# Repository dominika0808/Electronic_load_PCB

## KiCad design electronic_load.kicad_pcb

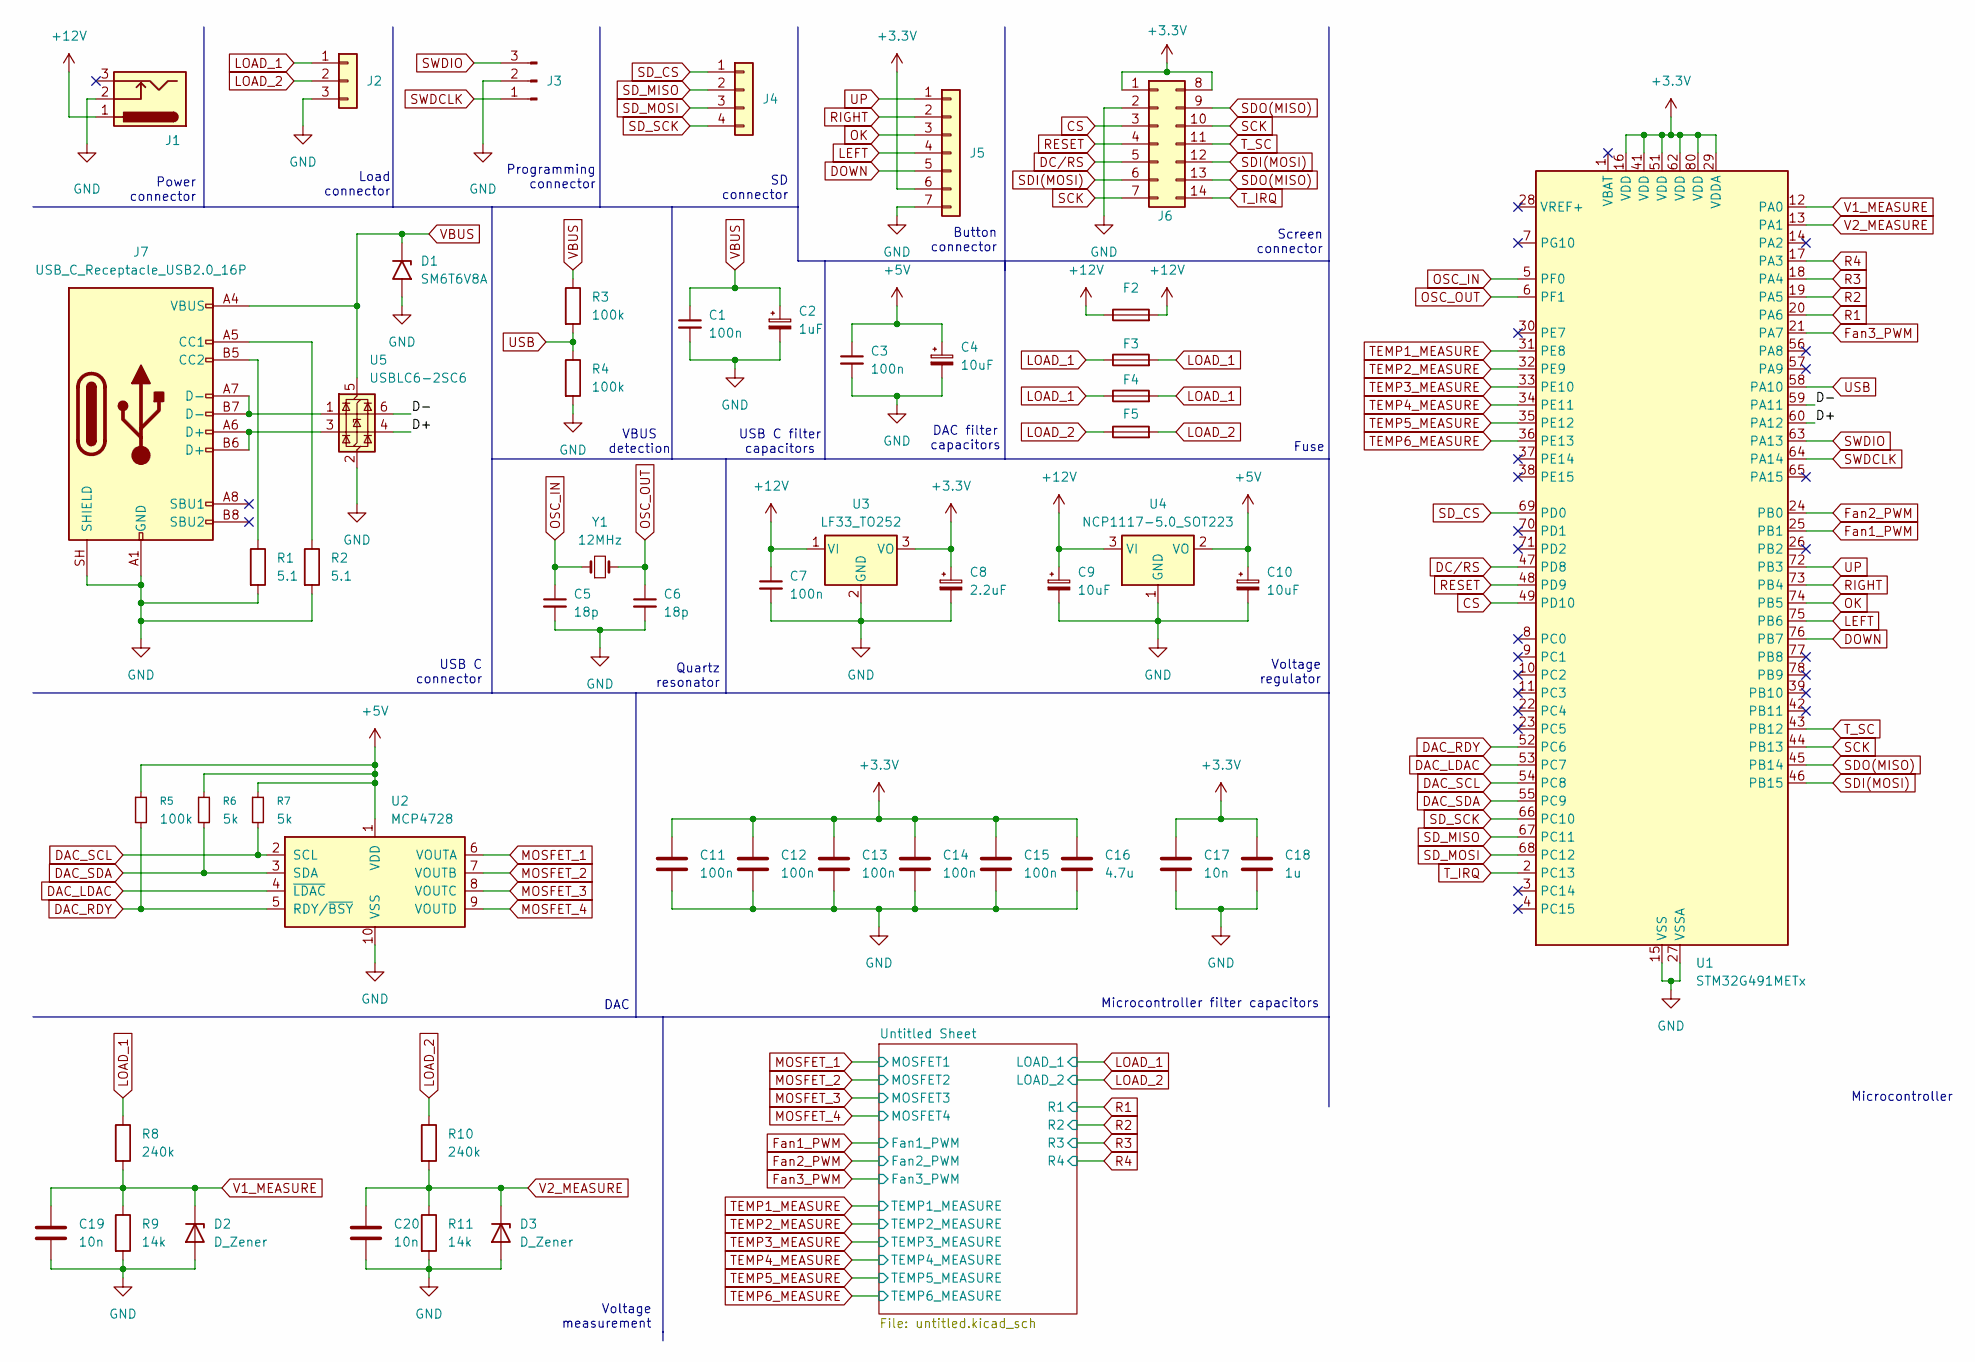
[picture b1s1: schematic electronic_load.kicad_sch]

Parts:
C1, C3, C7, C11, C12, C13, C14, C15: 100n; C_0805_2012Metric_Pad1.18x1.45mm_HandSolder
C2: 1uF; CP_EIA-3216-18_Kemet-A_HandSolder
C4: 10uF; CP_EIA-3216-18_Kemet-A_HandSolder
C5, C6: 18p; C_0805_2012Metric_Pad1.18x1.45mm_HandSolder
C8: 2.2uF; C_Elec_4x5.4
C9, C10: 10uF; C_Elec_4x5.8
C16: 4.7u; C_0805_2012Metric_Pad1.18x1.45mm_HandSolder
C17, C19, C20: 10n; C_0805_2012Metric_Pad1.18x1.45mm_HandSolder
C18: 1u; C_0805_2012Metric_Pad1.18x1.45mm_HandSolder
D1: SM6T6V8A; D_SMB
D2, D3: D_Zener; D_SOD-123F
F2, F3, F4, F5: Fuse; Fuse_1206_3216Metric_Pad1.42x1.75mm_HandSolder
J1: Barrel_Jack_Switch_Pin3Ring; BarrelJack_Wuerth_694106106102_2.0x5.5mm
J2: Conn_01x03; TerminalBlock_MaiXu_MX126-5.0-03P_1x03_P5.00mm
J3: Conn_01x03_Pin; PinHeader_1x03_P2.54mm_Vertical
J4: Conn_01x04; JST_EH_B4B-EH-A_1x04_P2.50mm_Vertical
J5: Conn_01x07; JST_EH_B7B-EH-A_1x07_P2.50mm_Vertical
J6: Conn_02x07_Top_Bottom; JST_PHD_B14B-PHDSS_2x07_P2.00mm_Vertical
J7: USB_C_Receptacle_USB2.0_16P; USB_C_Receptacle_GCT_USB4105-xx-A_16P_TopMnt_Horizontal
R1, R2: 5.1; R_0805_2012Metric_Pad1.20x1.40mm_HandSolder
R3, R4, R5: 100k; R_0805_2012Metric_Pad1.20x1.40mm_HandSolder
R6, R7: 5k; R_0805_2012Metric_Pad1.20x1.40mm_HandSolder
R8, R10: 240k; R_0805_2012Metric_Pad1.20x1.40mm_HandSolder
R9, R11: 14k; R_0805_2012Metric_Pad1.20x1.40mm_HandSolder
U1: STM32G491METx; LQFP-80_12x12mm_P0.5mm
U2: MCP4728; MSOP-10_3x3mm_P0.5mm
U3: LF33_TO252; TO-252-2
U4: NCP1117-5.0_SOT223; SOT-223-3_TabPin2
U5: USBLC6-2SC6; SOT-23-6
Y1: 12MHz; Crystal_HC49-4H_Vertical

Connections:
+3.3V: C8.1, C11.1, C12.1, C13.1, C14.1, C15.1, C16.1, C17.1, C18.1, J5.6, J6.1, J6.8, U1.16 (VDD), U1.29 (VDDA), U1.41 (VDD), U1.51 (VDD), U1.62 (VDD), U1.80 (VDD), U3.3 (VO); also elsewhere on the board
+5V: C3.1, C4.1, C10.1, R5.1, R6.1, R7.1, U2.1 (VDD), U4.2 (VO)
+12V: C7.1, C9.1, F2.1, F2.2, J1.1, U3.1 (VI), U4.3 (VI); also elsewhere on the board
/D+: U1.60 (PA12), U5.4 (I/O2)
/D-: U1.59 (PA11), U5.6 (I/O1)
CS: J6.3, U1.49 (PD10)
DAC_LDAC: U1.53 (PC7), U2.4 (~LDAC)
DAC_RDY: R5.2, U1.52 (PC6), U2.5 (RDY/~BSY)
DAC_SCL: R7.2, U1.54 (PC8), U2.2 (SCL)
DAC_SDA: R6.2, U1.55 (PC9), U2.3 (SDA)
DC/RS: J6.5, U1.47 (PD8)
DOWN: J5.5, U1.76 (PB7)
Fan1_PWM: U1.25 (PB1); also elsewhere on the board
Fan2_PWM: U1.24 (PB0); also elsewhere on the board
Fan3_PWM: U1.21 (PA7); also elsewhere on the board
GND: C1.2, C2.2, C3.2, C4.2, C5.2, C6.2, C7.2, C8.2, C9.2, C10.2, C11.2, C12.2, C13.2, C14.2, C15.2, C16.2, C17.2, C18.2, C19.2, C20.2, D1.2 (A2), D2.2 (A), D3.2 (A), J1.2, J2.3, J3.2, J5.7, J6.2, J7.A1 (GND), J7.A12 (GND), J7.B1 (GND), J7.B12 (GND), J7.SH (SHIELD), R1.2, R2.2, R4.2, R9.2, R11.2, U1.15 (VSS), U1.27 (VSSA), U1.40 (VSS), U1.50 (VSS), U1.61 (VSS), U1.79 (VSS), U2.10 (VSS), U3.2 (GND), U4.1 (GND), U5.2 (GND); also elsewhere on the board
LEFT: J5.4, U1.75 (PB6)
LOAD_1: F3.1, F3.2, F4.1, F4.2, J2.1, R8.1; also elsewhere on the board
LOAD_2: F5.1, F5.2, J2.2, R10.1; also elsewhere on the board
MOSFET_1: U2.6 (VOUTA); also elsewhere on the board
MOSFET_2: U2.7 (VOUTB); also elsewhere on the board
MOSFET_3: U2.8 (VOUTC); also elsewhere on the board
MOSFET_4: U2.9 (VOUTD); also elsewhere on the board
unnamed: J7.A5 (CC1), R2.1
unnamed: J7.B5 (CC2), R1.1
unnamed: J7.A6 (D+), J7.B6 (D+), U5.3 (I/O2)
unnamed: J7.A7 (D-), J7.B7 (D-), U5.1 (I/O1)
OK: J5.3, U1.74 (PB5)
OSC_IN: C5.1, U1.5 (PF0), Y1.1
OSC_OUT: C6.1, U1.6 (PF1), Y1.2
R1: U1.20 (PA6); also elsewhere on the board
R2: U1.19 (PA5); also elsewhere on the board
R3: U1.18 (PA4); also elsewhere on the board
R4: U1.17 (PA3); also elsewhere on the board
RESET: J6.4, U1.48 (PD9)
RIGHT: J5.2, U1.73 (PB4)
SCK: J6.7, J6.10, U1.44 (PB13)
SDI(MOSI): J6.6, J6.12, U1.46 (PB15)
SDO(MISO): J6.9, J6.13, U1.45 (PB14)
SD_CS: J4.1, U1.69 (PD0)
SD_MISO: J4.2, U1.67 (PC11)
SD_MOSI: J4.3, U1.68 (PC12)
SD_SCK: J4.4, U1.66 (PC10)
SWDCLK: J3.1, U1.64 (PA14)
SWDIO: J3.3, U1.63 (PA13)
TEMP1_MEASURE: U1.31 (PE8); also elsewhere on the board
TEMP2_MEASURE: U1.32 (PE9); also elsewhere on the board
TEMP3_MEASURE: U1.33 (PE10); also elsewhere on the board
TEMP4_MEASURE: U1.34 (PE11); also elsewhere on the board
TEMP5_MEASURE: U1.35 (PE12); also elsewhere on the board
TEMP6_MEASURE: U1.36 (PE13); also elsewhere on the board
T_IRQ: J6.14, U1.2 (PC13)
T_SC: J6.11, U1.43 (PB12)
UP: J5.1, U1.72 (PB3)
USB: R3.2, R4.1, U1.58 (PA10)
V1_MEASURE: C19.1, D2.1 (K), R8.2, R9.1, U1.12 (PA0)
V2_MEASURE: C20.1, D3.1 (K), R10.2, R11.1, U1.13 (PA1)
VBUS: C1.1, C2.1, D1.1 (A1), J7.A4 (VBUS), J7.A9 (VBUS), J7.B4 (VBUS), J7.B9 (VBUS), R3.1, U5.5 (VBUS)

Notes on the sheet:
Microcontroller
Screen connector
Voltage regulator
DAC
USB C connector
USB C filter capacitors
Load connector
Voltage measurement
DAC filter capacitors
Microcontroller filter capacitors
Programming connector
Quartz resonator
Fuse
SD connector
Power connector
VBUS detection
Button connector

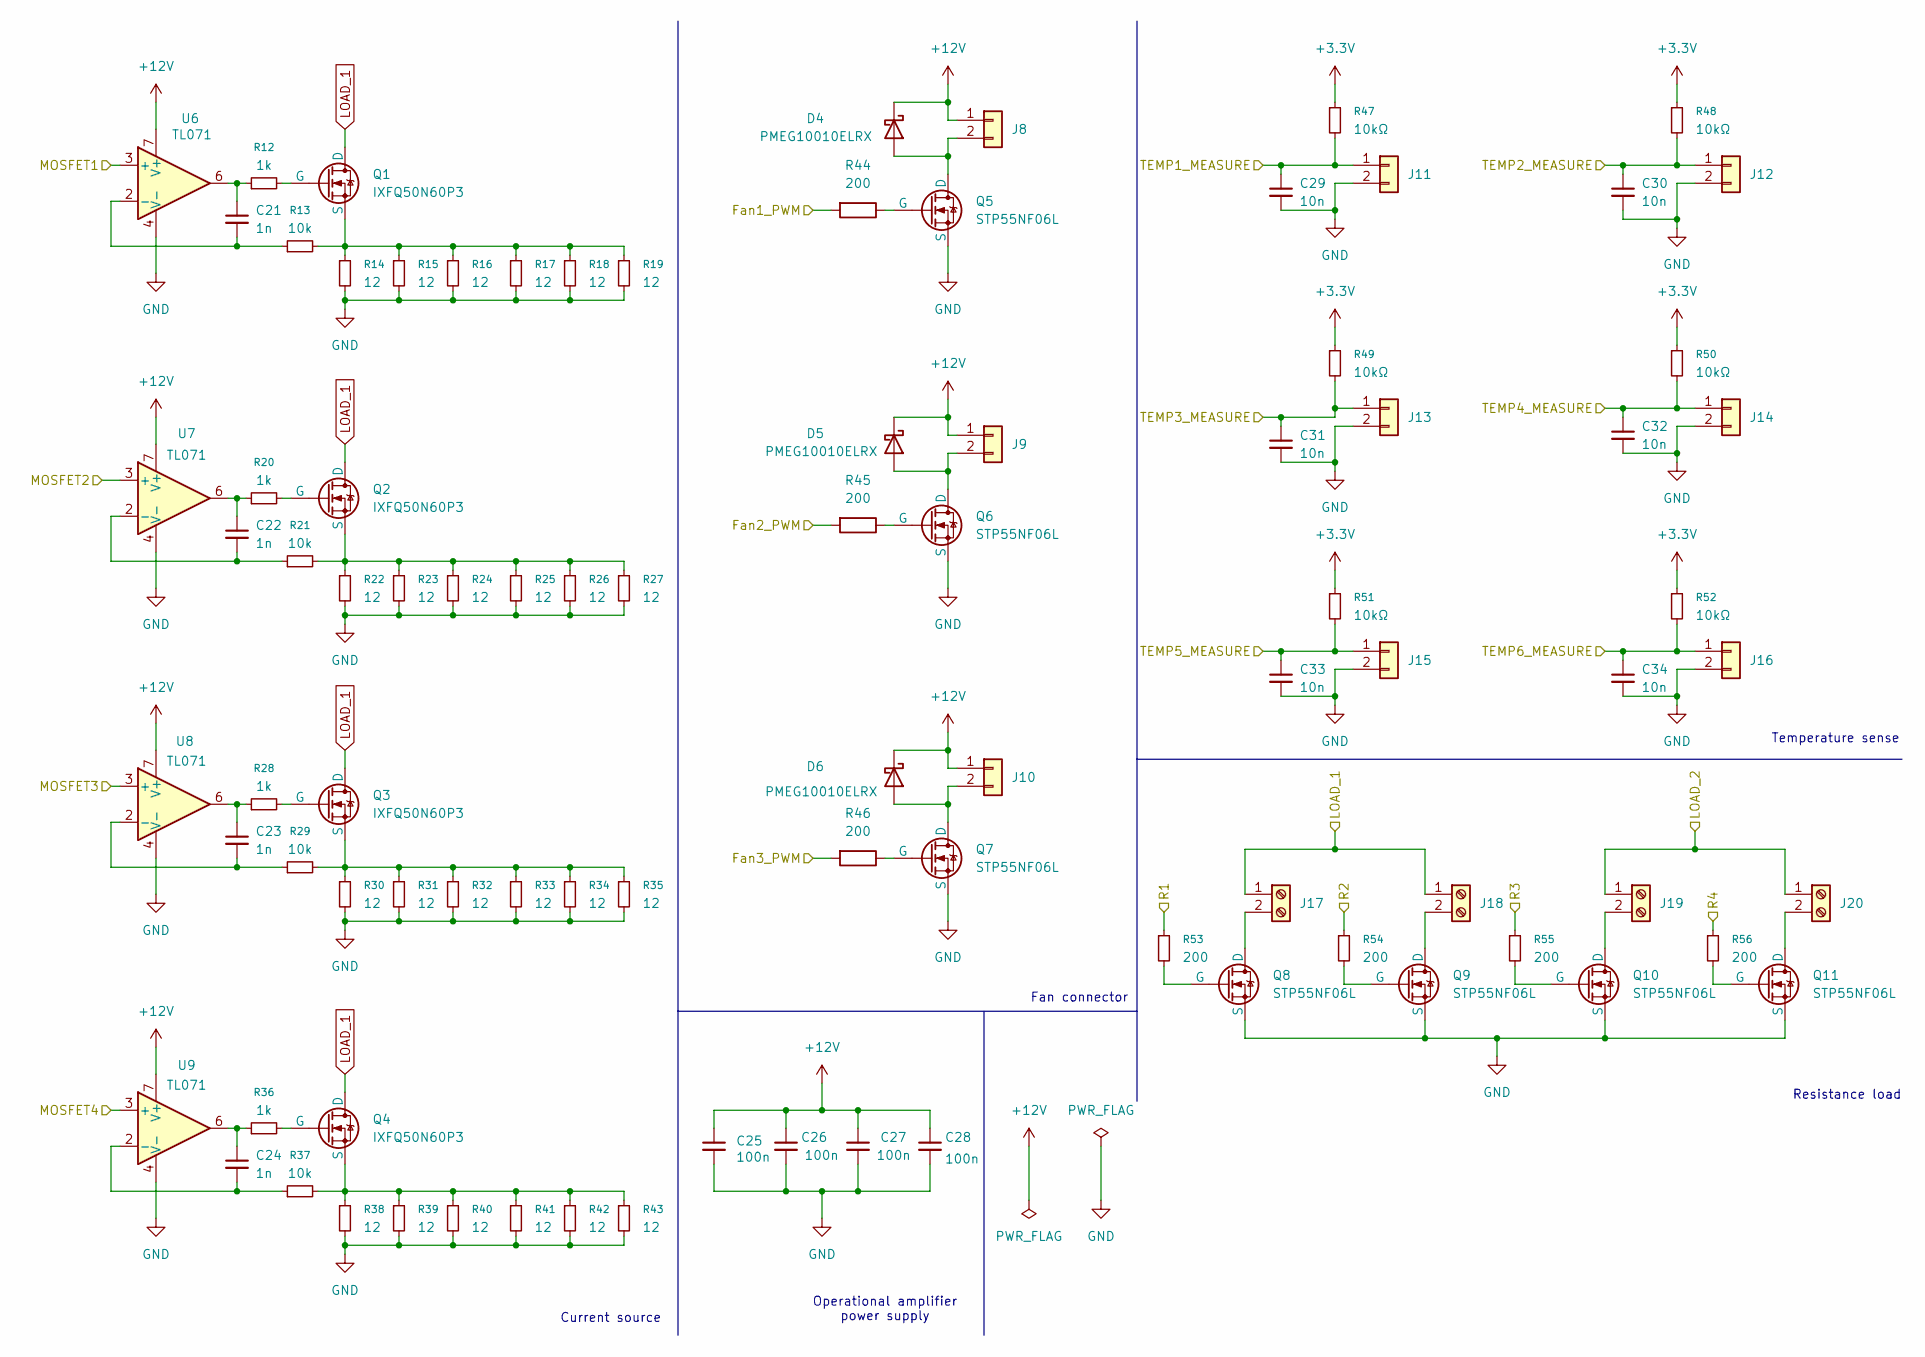
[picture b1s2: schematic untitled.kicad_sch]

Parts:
C21, C22, C23, C24: 1n; C_0805_2012Metric_Pad1.18x1.45mm_HandSolder
C25, C26, C27, C28: 100n; C_0805_2012Metric_Pad1.18x1.45mm_HandSolder
C29, C30, C31, C32, C33, C34: 10n; C_0805_2012Metric_Pad1.18x1.45mm_HandSolder
D4, D5, D6: PMEG10010ELRX; Nexperia_CFP3_SOD-123W
J8, J9, J10, J11, J12, J13, J14, J15, J16: Conn_01x02; JST_EH_B2B-EH-A_1x02_P2.50mm_Vertical
J17, J18, J19, J20: Screw_Terminal_01x02; TerminalBlock_MaiXu_MX126-5.0-02P_1x02_P5.00mm
Q1, Q2, Q3, Q4: IXFQ50N60P3; TO-3P-3_Vertical
Q5, Q6, Q7, Q8, Q9, Q10, Q11: STP55NF06L; TO-220-3_Vertical
R12, R20, R28, R36: 1k; R_0805_2012Metric_Pad1.20x1.40mm_HandSolder
R13, R21, R29, R37: 10k; R_0805_2012Metric_Pad1.20x1.40mm_HandSolder
R14, R15, R16, R17, R18, R19, R22, R23, R24, R25, R26, R27, R30, R31, R32, R33, R34, R35, R38, R39, R40, R41, R42, R43: 12; R_2512_6332Metric_Pad1.40x3.35mm_HandSolder
R44, R45, R46, R53, R54, R55, R56: 200; R_0805_2012Metric_Pad1.20x1.40mm_HandSolder
R47, R48, R49, R50, R51, R52: 10kΩ; R_0805_2012Metric_Pad1.20x1.40mm_HandSolder
U6, U7, U8, U9: TL071; SO-8_3.9x4.9mm_P1.27mm

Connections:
+3.3V: R47.1, R48.1, R49.1, R50.1, R51.1, R52.1; also elsewhere on the board
+12V: C25.1, C26.1, C27.1, C28.1, D4.1 (K), D5.1 (K), D6.1 (K), J8.1, J9.1, J10.1, U6.7 (V+), U7.7 (V+), U8.7 (V+), U9.7 (V+); also elsewhere on the board
Fan1_PWM: R44.2; also elsewhere on the board
Fan2_PWM: R45.2; also elsewhere on the board
Fan3_PWM: R46.2; also elsewhere on the board
GND: C25.2, C26.2, C27.2, C28.2, C29.2, C30.2, C31.2, C32.2, C33.2, C34.2, J11.2, J12.2, J13.2, J14.2, J15.2, J16.2, Q5.3 (S), Q6.3 (S), Q7.3 (S), Q8.3 (S), Q9.3 (S), Q10.3 (S), Q11.3 (S), R14.2, R15.2, R16.2, R17.2, R18.2, R19.2, R22.2, R23.2, R24.2, R25.2, R26.2, R27.2, R30.2, R31.2, R32.2, R33.2, R34.2, R35.2, R38.2, R39.2, R40.2, R41.2, R42.2, R43.2, U6.4 (V-), U7.4 (V-), U8.4 (V-), U9.4 (V-); also elsewhere on the board
LOAD_1: J17.1, J18.1, Q1.1 (D), Q2.1 (D), Q3.1 (D), Q4.1 (D); also elsewhere on the board
LOAD_2: J19.1, J20.1; also elsewhere on the board
MOSFET_1: U6.3 (+); also elsewhere on the board
MOSFET_2: U7.3 (+); also elsewhere on the board
MOSFET_3: U8.3 (+); also elsewhere on the board
MOSFET_4: U9.3 (+); also elsewhere on the board
unnamed: C21.1, R12.1, U6.6
unnamed: C22.1, R20.1, U7.6
unnamed: C23.1, R28.1, U8.6
unnamed: C24.1, R36.1, U9.6
unnamed: D4.2 (A), J8.2, Q5.1 (D)
unnamed: D5.2 (A), J9.2, Q6.1 (D)
unnamed: D6.2 (A), J10.2, Q7.1 (D)
unnamed: J17.2, Q8.1 (D)
unnamed: J18.2, Q9.1 (D)
unnamed: J19.2, Q10.1 (D)
unnamed: J20.2, Q11.1 (D)
unnamed: Q1.2 (G), R12.2
unnamed: Q1.3 (S), R13.2, R14.1, R15.1, R16.1, R17.1, R18.1, R19.1
unnamed: Q2.2 (G), R20.2
unnamed: Q2.3 (S), R21.2, R22.1, R23.1, R24.1, R25.1, R26.1, R27.1
unnamed: Q3.2 (G), R28.2
unnamed: Q3.3 (S), R29.2, R30.1, R31.1, R32.1, R33.1, R34.1, R35.1
unnamed: Q4.2 (G), R36.2
unnamed: Q4.3 (S), R37.2, R38.1, R39.1, R40.1, R41.1, R42.1, R43.1
unnamed: Q5.2 (G), R44.1
unnamed: Q6.2 (G), R45.1
unnamed: Q7.2 (G), R46.1
unnamed: Q8.2 (G), R53.2
unnamed: Q9.2 (G), R54.2
unnamed: Q10.2 (G), R55.2
unnamed: Q11.2 (G), R56.2
unnamed: C21.2, R13.1, U6.2 (-)
unnamed: C22.2, R21.1, U7.2 (-)
unnamed: C23.2, R29.1, U8.2 (-)
unnamed: C24.2, R37.1, U9.2 (-)
R1: R53.1; also elsewhere on the board
R2: R54.1; also elsewhere on the board
R3: R55.1; also elsewhere on the board
R4: R56.1; also elsewhere on the board
TEMP1_MEASURE: C29.1, J11.1, R47.2; also elsewhere on the board
TEMP2_MEASURE: C30.1, J12.1, R48.2; also elsewhere on the board
TEMP3_MEASURE: C31.1, J13.1, R49.2; also elsewhere on the board
TEMP4_MEASURE: C32.1, J14.1, R50.2; also elsewhere on the board
TEMP5_MEASURE: C33.1, J15.1, R51.2; also elsewhere on the board
TEMP6_MEASURE: C34.1, J16.1, R52.2; also elsewhere on the board

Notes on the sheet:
Current source
Temperature sense
Resistance load
Fan connector
Operational amplifier power supply

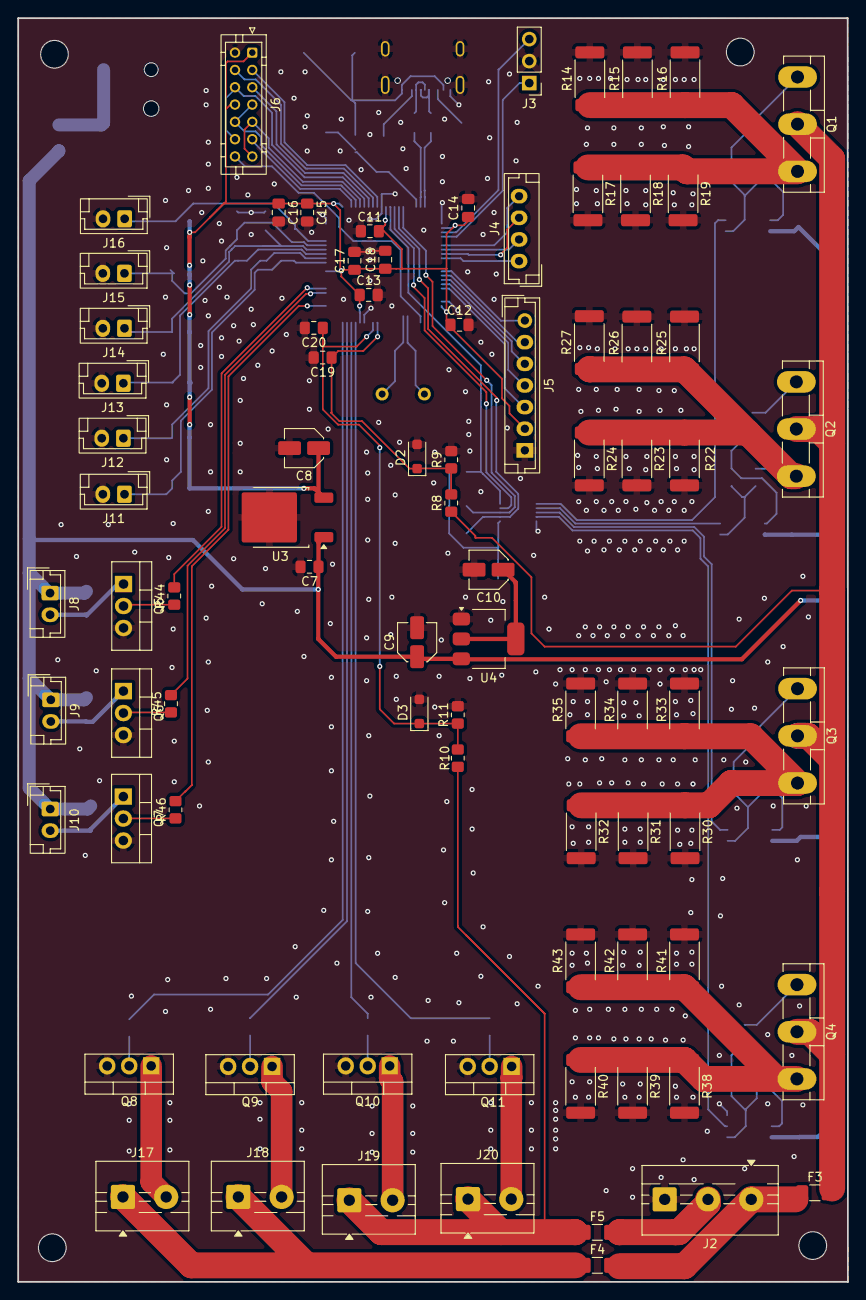
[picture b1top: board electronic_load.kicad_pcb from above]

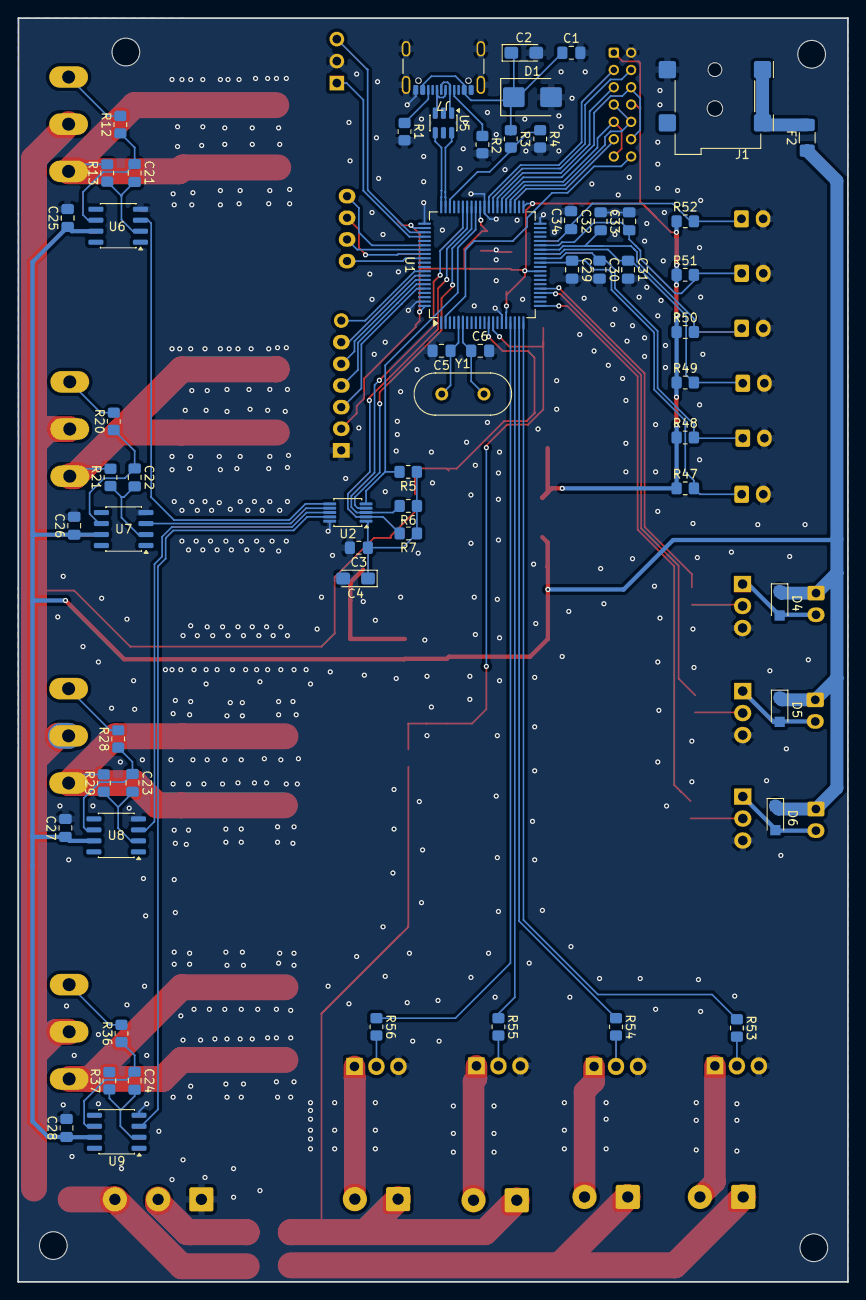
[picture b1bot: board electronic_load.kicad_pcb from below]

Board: 2 copper layers, 95.9 x 146.0 mm, 141 parts (60 on the bottom side), 88 nets.
